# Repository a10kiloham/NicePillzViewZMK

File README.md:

# Nice Pillz View - ZMK config and PCB

## Overview
ZMK configuration and PCB for the Nice Pillz board, a nice!nano based controller for the Kinesis
Advantage, extended with a nice!view display. Based on https://github.com/nol00p/NicePillz.
The keymap follows the Kinesis Advantage legends and targets Windows.

## Hardware
- The PCB in `kicad/` is updated for the display header and the switch LED, see [PCB](#pcb--ordering-from-jlcpcb) below.
- For the original design and the thumb pads, see https://github.com/nol00p/NicePillz
- For the rubber function buttons replacement with PCB for the older Advantage 1, these are excellent: https://github.com/bluelightning32/kinesis-fn
- `housing_stl/niceview_cover.stl` is a printable cover that holds the nice!view in the Kinesis top shell.

## Features supported
- [x] ZMK Studio
- [x] nice!view display (vertical): battery/charging, WPM, BT profile, layer, lock indicators
- [x] Leader key
- [x] Caps word
- [x] zmk-helpers
- [x] Layer cycle key
- [x] Macros, with unicode support
- [ ] Combos (supported but not yet tested)

## Quick reference
| Key | Function |
| --- | --- |
| F13 (the Print Screen key) | Unlock ZMK Studio |
| F14 (the Scroll Lock key) | F14; with Shift: output between Bluetooth and USB |
| Pause key, right of F14 | Print Screen |
| Keypad key (F16) | Layer: steps to the next layer in a loop |
| Function key (right thumb, left of Right Ctrl) | FN layer while held with another key; tapped alone, same as the Layer key |
| Program (top right) | SYSTEM layer while held |
| Program + F1, F2, F3, F4 | Select Bluetooth profile 1 to 4 |
| Program + F8 | Forget all four Bluetooth pairings |
| Program + Esc or = | Bootloader, for flashing |
| Program + Caps Lock key | Caps Lock |
| Program + left Shift | Leader key |
| Caps Lock key, left side | F5 |
| Key beneath X | Win (GUI) |
| Left thumb, top | Left Ctrl, Alt |
| Right thumb, top | Function, Right Ctrl |
| Left thumb, bottom | Backspace, Delete |
| Right thumb, bottom | Enter, Space |

Notes:

- F13 and F14 are the Print Screen and Scroll Lock positions. Scroll Lock and Pause are not on
  the base layer.
- The Layer key loops through DEFAULT, LOWER, FN, SYSTEM and BLUETOOTH, which are dots 1 to 5 on
  the display. A tap of the Function thumb key does the same.
- F13, F14, Print Screen, Layer and Program do the same thing on every layer.
- Pairing: hold Program and tap F1 to F4 to pick a profile; a free profile advertises straight
  away, so pair from the PC. Program + F8 forgets all four pairings at once; remove `NicePillz`
  from the PC's Bluetooth list too before pairing again.
- Left Shift and right Shift are plain Left Shift and Right Shift. Backspace, Delete and Enter are
  plain keys too, so they repeat when held.
- ZMK cannot switch the Bluetooth radio off. Shift + F14 switches the output between Bluetooth
  and USB instead; with USB selected and no cable, the keyboard sends nothing. The display shows
  a USB symbol while USB is selected.
- The media keys on FN are quickest with the Function thumb key held: Function + F10 is
  play/pause.
- The display shows the Bluetooth logo on the left with the profile number beside it at the same
  size. A small tick means connected, a cross means not connected, and no mark means the profile
  is free and advertising.

### Label for the bottom of the keyboard
[`KEYS.md`](KEYS.md) is the one-page key reference to print. `docs/bottom-label.txt` is a
condensed version that fits a 3 x 3 inch label in a monospace font at 8 pt.

```
NICE PILLZ VIEW - QUICK REFERENCE

TOP RIGHT  F13 Unlock Studio |
  F14 | PrtSc | Layer | Program
  Shift+F14  Bluetooth <-> USB

SYSTEM     hold Program +
  F1 F2 F3 F4  Bluetooth device 1-4
  F8        forget all pairings
  Esc or =  flash mode (NICENANO)
  Caps key  Caps Lock

LAYER  next layer, loops 1 to 5
  1 Default 2 Lower 3 FN 4 System 5 BT
  Caps Lock key = F5, under X = Win
  L thumb: Ctrl Alt / Bksp Del
  R thumb: Func Ctrl / Enter Spc
  Func held + key = FN, tap = Layer

EDIT KEYS  https://zmk.studio
github.com/a10kiloham/NicePillzViewZMK
```

## Keymap (Windows)
`config/nicepillz.keymap`. The base layer follows the key legends, with these choices:

- Caps Lock position is **F5**. Left Shift is Left Shift and right Shift is Right Shift, both plain keys.
- The letter rows are plain keys, no home-row mods. The key beneath X, left of the Left arrow, is
  **Win**.
- Thumbs: Ctrl, Alt | Function, Ctrl on top; Backspace, Delete | Enter, Space on the big keys.
  **Function** held with another key = that key on the FN layer; tapped alone = the Layer key.
- Top right keys after F12: **Studio unlock** (F13), **F14** (Shift + F14 = Bluetooth/USB
  output), **Print Screen**, **Layer**, **Program**, the same on every layer. Layer steps to the
  next layer in a loop: DEFAULT, LOWER, FN, SYSTEM, BLUETOOTH. **Program** held = SYSTEM.
- LOWER: F1/F2 previous/next virtual desktop, F3 task view, F4 new desktop, F8 input language,
  F9/F10 move window to the left/right monitor, F11 show desktop, F12 close desktop; arrows on
  H J K L; Ctrl+A/Z/X/C/V on the left hand.
- FN: F6 mute, F7 volume down, F8 volume up, F9 previous, F10 play/pause, F11 next, F12 stop.
- SYSTEM (hold Program): **ESC or = = bootloader** (flashing mode), **F1-F4 select Bluetooth
  profiles 1-4**, **F8 forgets all four Bluetooth pairings**, the Caps Lock key is **Caps Lock**,
  left Shift is the **leader** key.
- BLUETOOTH (dot 5): the same F1-F4 and F8 keys without holding Program; everything else types
  normally.

### ZMK Studio
Open [zmk.studio](https://zmk.studio) in Chrome or Edge (Web Serial; Firefox does not work) or the
Studio desktop app, with the keyboard plugged in over USB and running normally, and choose the
`NicePillz` serial device. The keyboard starts locked: press **F13** to unlock, then the keymap
becomes editable. Program+Esc is *not* the Studio key, it reboots into the bootloader for
flashing, and Studio cannot connect while the `NICENANO` drive is showing.
- Leader sequences (hold Program, tap left Shift, then type the sequence): `4` euro sign,
  `D 1`/`D 2` previous/next desktop, `W 1`/`W 2` move window left/right. Unicode macros (accented letters) type through [WinCompose](https://github.com/samhocevar/wincompose),
  which must be installed on the PC.

Keys edited in ZMK Studio are stored on the keyboard and override this file. Flashing a firmware
whose keymap file has changed discards those stored edits automatically on the first boot
(`boards/shields/nicepillz/keymap_rev.c`), so the flashed keymap is always the default. Flashing
the same keymap again keeps the Studio edits; *Restore Stock Settings* in Studio removes them.

## Battery level
Battery reporting is enabled so the level is visible in the OS. Bluetooth and power status update
too for a better experience.

## Display (nice!view)
The board carries a nice!view (Sharp 160x68 memory LCD), mounted vertically with the header pins
at the bottom. The status screen (`boards/shields/nicepillz/view_draw.c`) is drawn upright and
rotated into the panel, top to bottom:

1. **Battery** - a battery-shaped gauge plus the percentage. On USB power the gauge is replaced by
   a lightning bolt and the word *Charging*.
2. **Words per minute** - a graph of the last 24 samples (one every 5 s, so two minutes of
   history, auto-scaled) with the current value in the corner (`CONFIG_NICEPILLZ_WPM_INTERVAL_MS`).
3. **Output** - a Bluetooth logo on the left with the active profile number beside it at the
   same size, then a small tick (connected) or cross (bonded but not connected); a USB symbol
   when USB is the selected output.
4. **Layer** - five numbered dots; the filled one is the highest active layer (1-5).
5. **Lock indicators** - *Caps Lock*, *Num Lock*, *Scrl Lock* boxes in a row, only the active
   ones; they use the host's HID lock state.
6. **Modifiers** - *Ctrl Alt Shift Win Prgm* along the bottom edge; each lights up while the key
   is held. *Prgm* is the Program key, i.e. the SYSTEM layer
   (`CONFIG_NICEPILLZ_PROGRAM_LAYER`).

Options (`boards/shields/nicepillz/Kconfig.defconfig`, override in `boards/shields/nicepillz/nicepillz.conf`):
- `CONFIG_ZMK_DISPLAY=n` disables the display entirely.
- `CONFIG_NICEPILLZ_DISPLAY_INVERTED=y` draws white on black.
- `CONFIG_NICEPILLZ_DISPLAY_LANDSCAPE=y` uses the landscape layout: the picture is turned 90
  degrees clockwise, for a display mounted with the header pins on the right. The same
  elements are rearranged for the 160x68 shape: battery, WPM graph and output on top, layer dots
  and modifiers bottom left, lock indicators bottom right.

`tools/preview/build.sh` compiles the real drawing code against LVGL on the host and writes
`docs/display-preview.png`, so layout changes can be checked without flashing.

Wiring: the display shares the SPI bus with the 74HC595 column driver. SCK = P0.11 (D7),
MOSI = P0.24 (D5), display CS = P1.01, powered from the nice!nano VCC pin (switched off in deep
sleep together with the shift register). On v10 boards the J9 header is in the nice!view's own pin
order (CS, GND, 3V3, SCK, MOSI, top to bottom) so the display plugs straight in. v9 boards have J9
as GND, MOSI, CS, SCK, 3V3 and need the display wired pin by pin.

## LEDs and sleep
- **PWR** (D1): on while the board is awake, driven by the spare 74HC595 output (P1.01 is the
  display chip select). Slow flash after 5 min idle, off in deep sleep.
- **BLE** (D2): on while the active Bluetooth profile is connected, off when idle or asleep.
- **Switch LED** header (v10): powers the LED inside an illuminated power switch whenever the board
  has power, see [PCB](#pcb--ordering-from-jlcpcb).

Sleep after 5 min idle: any key resumes. Deep sleep after 20 min: press the Esc key (0,0) to wake.

## PCB / ordering from JLCPCB
`kicad/nice_pillz_niceview_v10.kicad_pcb` is the board (KiCad 10). Ready-to-upload fabrication
files, exported with `kicad-cli` from the committed board (DRC: 0 unconnected items), are in
`kicad/jlcpcb/` and attached to the [v10 release](https://github.com/a10kiloham/NicePillzViewZMK/releases/tag/v10):

- `nice_pillz_niceview_v10_jlcpcb.zip` - upload this as-is to JLCPCB (2 layers, 1.6 mm).
- `gerbers/` - the same files unzipped: copper, mask, paste, silkscreen, board outline (Protel
  extensions), Excellon drills split into PTH / NPTH, and a drill map.

## 

Changes in v10 (silkscreen v1.1) compared with the v9 boards already made:

- **J9 display header** is ordered CS, GND, 3V3, SCK, MOSI to match the nice!view (see Display above).
  Pad numbers and nets are unchanged, so the schematic still matches; only the pad positions inside
  the footprint instance moved (re-importing the footprint from the library would undo this).
- **Switch LED header** replaces the external reset terminal at the top of the board (same two holes).
  It is a 2-pin 2.54 mm header for the LED inside an illuminated power switch: the square pin (marked
  `+`) is the LED anode, fed from the switched 3.3 V rail through **R3** next to it; the round pin is
  GND. Fit R3 to suit the LED: 330 R for red/green/yellow (about 4 mA), 100 R for blue/white. The
  LED is on whenever the keyboard is powered: off when the power switch is off, off in deep sleep
  (the firmware cuts the 3.3 V rail), and on while charging over USB even with the switch off. The
  onboard reset push button is unchanged; there is no longer a terminal for an external reset.
- D1/D2 are labelled LED_PWR / LED_BLE on the fab layer.

## Hardware bill of materials
Mostly common parts and a bit of soldering.

| Position          | Part                                   | Qty | Notes |
| ----------------- | -------------------------------------- | --- | ----- |
| J1-J4, J7, J8     | Molex 39-53-2135, 13-way               | 6   | [Mouser](https://eu.mouser.com/ProductDetail/Molex/39-53-2135?qs=cm0cgiBciNYI3jeMaEn0Ng%3D%3D) |
| J5, J6            | 1x10 pin header, 2.54 mm               | 2   | |
| J9                | nice!view                              | 1   | v10: plugs onto the header; v9: wire pin by pin |
|                   | JST-EH 5-pin connector                 | 2   | display lead |
|                   | Mill Max 0305 sockets
| U1                | nice!nano v2                           | 1   | |
| U2                | 74HC595                                | 1   | [Amazon](https://www.amazon.fr/dp/B093Y2MQGV) |
| U2                | Mill Max style connected sockets       | 1   | |
| D1, D2            | LED (PWR, BLE)                         | 2   | [Amazon](https://www.amazon.fr/dp/B005Q2MZ4Q) |
| R1, R2            | 4.7 k resistor                         | 2   | sets LED brightness, smaller = brighter (1 k is clearly visible at 3.3 V) |
| R3                | 330 R (red/green/yellow) or 100 R (blue/white) | 1 | switch LED series resistor |
| Battery, Ext. PWR Switch | 2-pin screw terminal, 2.54 mm   | 2   | v9 boards have a third one for an external reset |
| Switch LED        | 1x2 pin header, 2.54 mm                | 1   | v10 only |
|                   | 6 mm tactile reset button              | 1   | |
|                   | Illuminated power switch               | 1   | Adafruit; LED leads go to the Switch LED header on v10 |
|                   | 3.7 V LiPo battery, 2000 mAh           | 1   | [Amazon](https://www.amazon.fr/dp/B08214DJLJ) |
|                   | USB-C panel mount extension            | 1   | [AliExpress](https://fr.aliexpress.com/item/1005009401577622.html) |
|                   | Display cover, 3D printed              | 1   | `housing_stl/niceview_cover.stl` |

## 3D Printed Parts
Thanks to `happy panda` for their design here: https://www.printables.com/model/1622734-kinesis-advantage-thumb-millmax-mod
Remixed here if you're using stabilizers: https://www.printables.com/model/1842360-kinesis-thumb-cluster-pcb-replacement-millz-mod-co

## Assembly
A small hot plate (Miniware MHP30 or a cheaper clone) makes the SMD parts much easier.
LED orientation: with the LEDs facing up, the arrow points to the left across the two pads.

## Firmware
GitHub Actions builds the firmware on every push (`build.yaml`). Prebuilt images for the
nice!nano v2 are in `firmware/` and on the release page:

- `nicepillz_nice_nano_v2.uf2` - black on light (default).
- `nicepillz_nice_nano_v2_inverted.uf2` - light on black display (`CONFIG_NICEPILLZ_DISPLAY_INVERTED=y`).
- `nicepillz_nice_nano_v2_landscape.uf2` - landscape display, black on light (`CONFIG_NICEPILLZ_DISPLAY_LANDSCAPE=y`).
- `nicepillz_nice_nano_v2_landscape_inverted.uf2` - landscape display, light on black.
- `nicepillz_nice_nano_v2_reset.uf2` and `nicepillz_nice_nano_v2_landscape_reset.uf2` - the normal
  firmware that also erases every stored setting each time it boots: Bluetooth pairings, the
  keymap saved by ZMK Studio, and the selected output. The keys and the display keep working.
- `nicepillz_nice_nano_v2_usblog.uf2` and `nicepillz_nice_nano_v2_landscape_usblog.uf2` - the
  portrait and landscape firmware with debug logging over USB, for finding out what the keyboard
  thinks it sent (see below). Slower, use only to debug.

**Into flash mode:** hold Program and tap Esc or =. If the keymap is not responding, double-tap
the reset button on the board. Either way the `NICENANO` drive appears; copying a `.uf2` onto it
flashes and restarts the keyboard.

For Bluetooth trouble, Program + F8 (forget all pairings) is usually enough. To erase every
setting, flash the `_reset` firmware for your display orientation, let it boot once, then enter
flash mode again and flash the normal firmware. While the `_reset` firmware is loaded the settings
are wiped on every boot, so nothing it pairs with is kept. Remove the keyboard from each
computer's Bluetooth device list before pairing again.

### Debug logging over USB
Flash `nicepillz_nice_nano_v2_usblog.uf2` (portrait) or `nicepillz_nice_nano_v2_landscape_usblog.uf2`
(landscape), built with `-S zmk-usb-logging` and `CONFIG_ZMK_LOG_LEVEL_DBG=y`. The keyboard then shows up as two serial ports: one is ZMK Studio,
the other streams the log. Open the log port at any baud rate, for example in PowerShell:

```
[System.IO.Ports.SerialPort]::GetPortNames()      # find the new COM port, try each
$p = New-Object System.IO.Ports.SerialPort COM5, 115200; $p.Open()
while ($true) { $l = $p.ReadLine(); if ($l -match "keycode|hold-tap|hold_tap") { $l } }
```

Every key press and release appears as `hid_listener_keycode_pressed ... keycode 0x..`:
0xE0 to 0xE7 are the modifier keys (E0 Left Ctrl, E1 Left Shift, E2 Left Alt, E3 Left Win, E4 to
E7 the right-hand ones). The hold-tap lines name the key position of the few remaining hold-taps
(the Bluetooth layer's 9 key) and say whether they were decided as a hold or a tap, and why.

## Credits
- https://github.com/nol00p/ZMK-NicePillz
- https://github.com/dcpedit/pillzmod
- https://github.com/masters3d/zmk-config-pillzmod-nicenano
- https://github.com/urob/zmk-leader-key
- https://github.com/urob/zmk-helpers

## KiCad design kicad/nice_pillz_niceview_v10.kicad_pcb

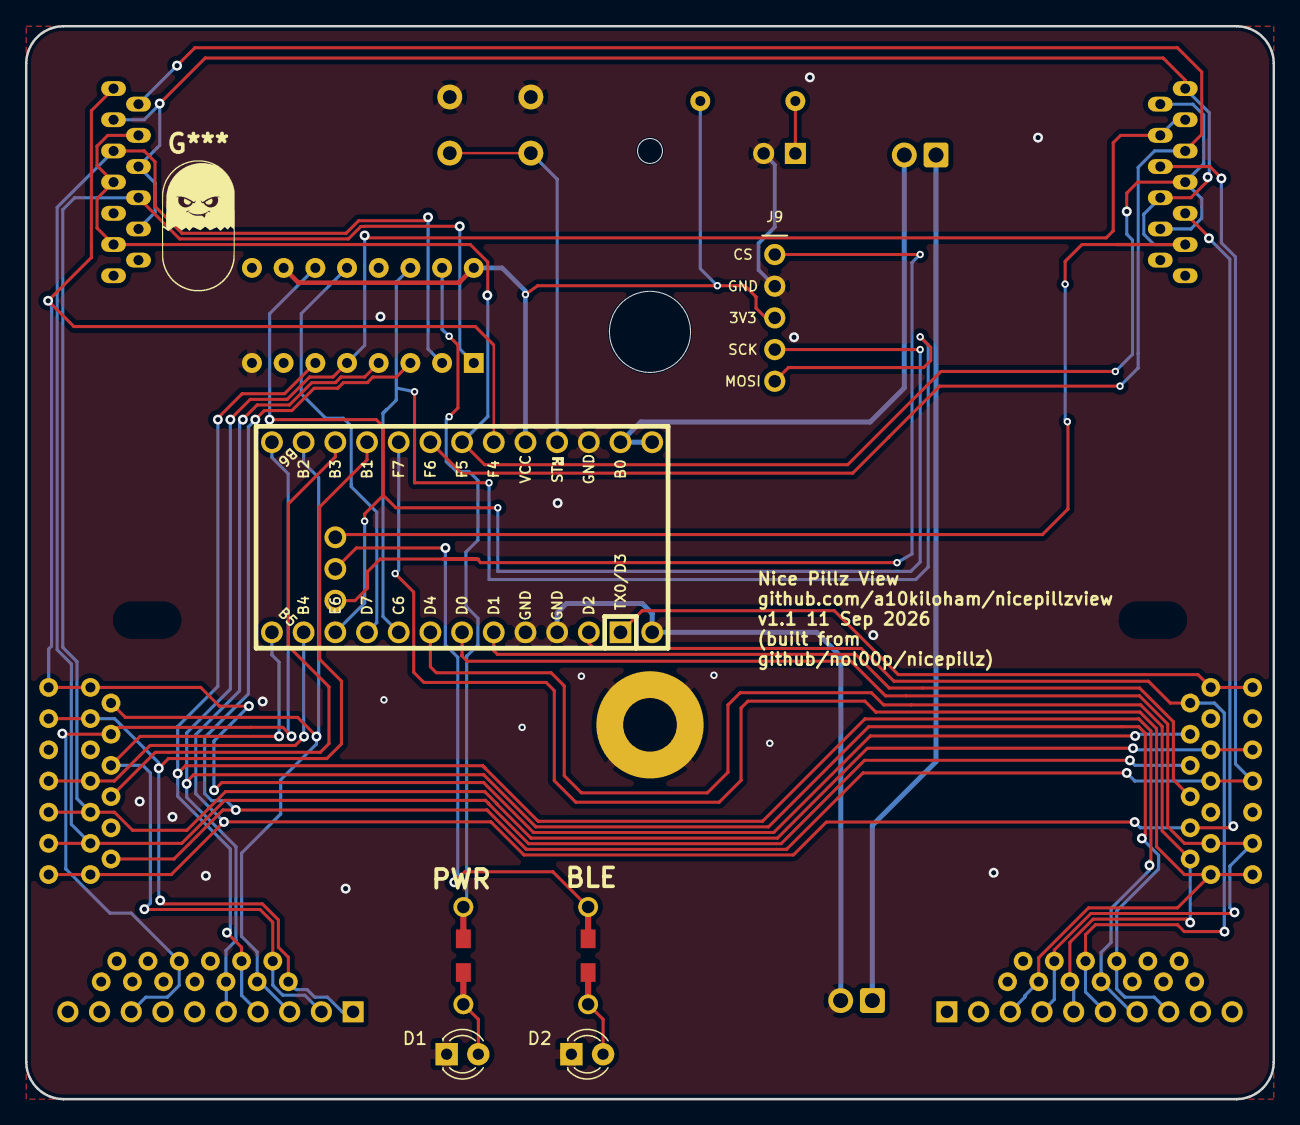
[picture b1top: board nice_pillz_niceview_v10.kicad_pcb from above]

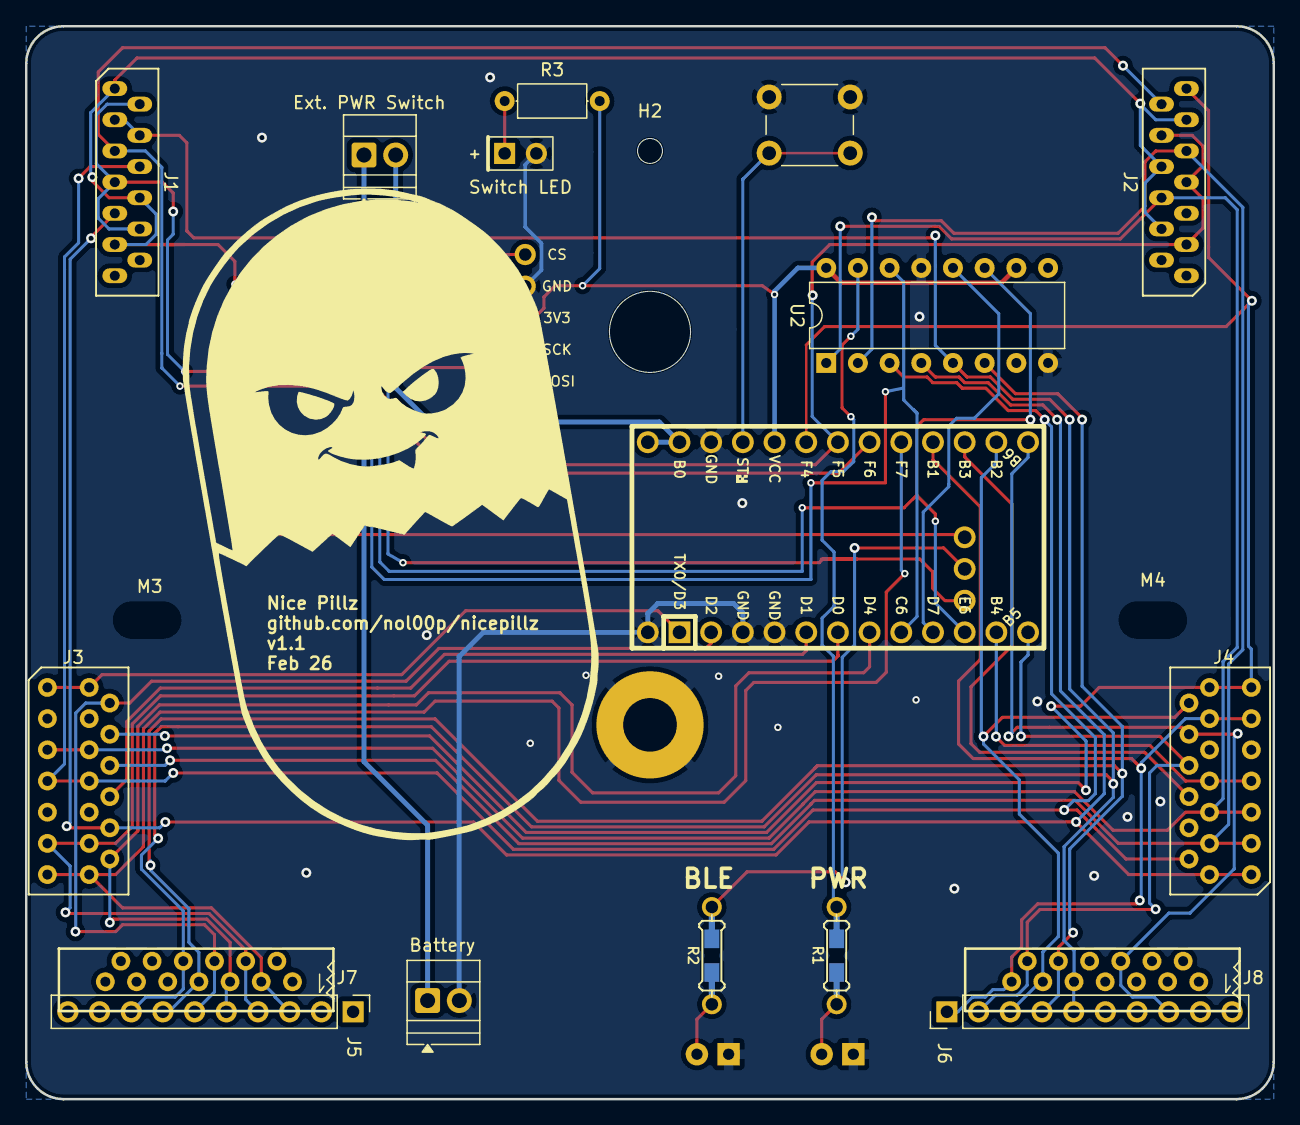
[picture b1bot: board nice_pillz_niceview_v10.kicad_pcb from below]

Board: 2 copper layers, 100.0 x 86.0 mm, 24 parts (20 on the bottom side), 35 nets.

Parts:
Battery: TerminalBlock_Xinya_XY308-2.54-2P_1x02_P2.54mm_Ho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; TerminalBlock_Xinya_XY308-2.54-2P_1x02_P2.54mm_Horizontal
D1: LED_PWR; LED_D3.0mm
D2: LED_BLE; LED_D3.0mm
Ext. PWR Switch: TerminalBlock_Xinya_XY308-2.54-2P_1x02_P2.54mm_Ho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; TerminalBlock_Xinya_XY308-2.54-2P_1x02_P2.54mm_Horizontal
H1: mounting pad; MountingHole_4.3mm_M4_Pad
H2: mounting pad; MountingHole_2mm
J1, J2: Conn_01x13; Molex_0039532135
J3, J4: Conn_01x13; Molex_039532134
J5, J6: Conn_01x10; Pin_Header_Straight_1x10_Pitch2.54mm
J7, J8: Conn_01x13; 39-53-2135
J9: NiceView; NiceView_1x05_P2.54mm_V
M1: MountingHole_6.4mm_M6
M3, M4: MountingHole_4.3mm_M4
R1, R2: R_US; Resistor-Hybrid
R3: 330R; R_Axial_DIN0207_L6.3mm_D2.5mm_P7.62mm_Horizontal
Switch LED: PinHeader_1x02_P2.54mm_Vertical
U1: nice!nanov2; nice_nano_v2
U2: 74HC595; DIP-16_W7.62mm

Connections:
+5V: J9.5, R3.2, U1.21 (VCC), U2.10 (~SRCLR), U2.16 (VCC)
/COL_0: J2.13, J3.4, J4.13, U1.20 (A3/PF4)
/COL_1: J2.6, J3.5, J4.5, U2.1 (QB)
/COL_2: J2.9, J3.6, J4.3, U2.2 (QC)
/COL_3: J1.6, J3.7, J4.2, U2.3 (QD)
/COL_4: J1.9, J3.10, J4.1, U2.4 (QE)
/COL_5: J1.3, J1.4, J5.8, J6.5, J7.8, J8.9, U2.5 (QF)
/COL_6: J5.7, J6.4, J7.7, J8.10, U2.6 (QG)
/LATCH: U1.9 (6/PD7), U2.12 (RCLK)
/LED_CAPS_LOCK: J9.3, U1.26 (D5)
/LED_NUM_LOCK: R2.2, U1.27 (C7)
/PWR_LED: R1.2, U2.15 (QA)
/ROW_0: J4.6, U1.15 (14/PB3)
/ROW_1: J4.7, U1.11 (8/PB4)
/ROW_2: J4.8, J6.2, J8.12, U1.12 (9/PB5)
/ROW_3: J4.10, J6.8, J8.6, U1.13 (10/PB6)
/ROW_4: J4.11, J6.1, J8.13, U1.16 (15/PB1)
/ROW_5: J4.12, J6.3, J8.11, U1.14 (16/PB2)
/ROW_6: J3.13, J5.3, J7.3, U1.17 (A0/PF7)
/ROW_7: J3.11, J5.4, J7.4, U1.6 (3/PD0)
/ROW_8: J3.12, J5.5, J7.5, U1.7 (4/PD4)
/ROW_9: J3.2, J5.6, J7.6, U1.2 (RX1/PD2)
/ROW_10: J3.1, U1.1 (TX0/PD3)
/ROW_11: J3.8, U1.5 (2/PD1)
/ROW_12: J1.5, J2.12, U1.18 (A1/PF6)
/ROW_13: J1.1, J1.8, J1.11, J2.4, J2.8, J2.11, U1.28 (F1)
/ROW_14: J1.2, J1.7, J1.10, J2.3, J2.7, J2.10, U1.19 (A2/PF5)
/SPI_MOSI: J9.2, U1.8 (5/PC6), U2.14 (SER)
/SPI_SCK: J9.4, U1.10 (7/PE6), U2.11 (SRCLK)
/SW_LED: R3.1, Switch LED.1
BAT: Ext. PWR Switch.2, U1.24 (B0)
BAT+: Battery.1, Ext. PWR Switch.1
GND: Battery.2, D1.1 (K), D2.1 (K), H1.1, J9.1, Switch LED.2, U1.3 (GND), U1.4 (GND), U1.23 (GND), U2.8 (GND), U2.13 (~OE)
unnamed: D1.2 (A), R1.1
unnamed: D2.2 (A), R2.1
